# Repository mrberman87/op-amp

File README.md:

# Discrete Operational Amplifier — Two-Stage, LCSC-sourced (Rev E)

A **discrete-component operational amplifier** built only from parts LCSC
stocks. No op-amp ICs: transistors, resistors and capacitors.

Rev E adds a **second gain stage** to Rev D. That is what makes the 60 dB
requirement reachable: the single-stage Rev D topped out at 58.5 dB because
the BFP420's Early voltage (`VAF = 28.4 V`) sets its intrinsic gain at
~60.7 dB. The second stage raises the **open-loop** gain to ~110 dB, so a
60 dB closed loop has ~50 dB of loop gain, and the Miller capacitor sets the
bandwidth.

---

## 1. Target vs. achieved

| Parameter | Target | Rev E | Verdict |
|---|---|---|---|
| Closed-loop gain | 60 dB (1000 V/V) | **59.9 dB** | met |
| −3 dB bandwidth | DC → 10 MHz | **DC → 11.5 MHz** | met |
| Gain at 10 MHz | 60 dB | **58.0 dB** (−2 dB) | ~met |
| Open-loop gain | — | **~110 dB** | — |
| Phase margin | > 45° | **~65°** (no closed-loop peaking) | met |
| Output stage | push-pull | **class-AB complementary** | met |
| Supplies | ±15 V | ±15 V | — |
| ERC | clean | **0 errors / 0 warnings** | met |
| Device stress | no overstress | **no VCEO or >50 % Pd violations** | met |

The closed-loop response is flat (no peaking) from DC to ~1 MHz, −2 dB at
10 MHz, −3 dB at 11.5 MHz. The low-frequency gain is 59.4 dB at 0.01 Hz,
so the AC bypass in stage 2 does **not** introduce an audio-band rolloff in
closed loop.

---

## 2. Topology

```
 IN+ ─┐
      ├─ Q1/Q2 BFP420 diff pair ── Q4/Q6 MMBTH81 mirror ── c2
 IN− ─┘   (Q3 ref-side cascode)    (Q5/Q7 cascodes, Q8 helper)
                                                             │
                        ┌────────────────────────────────────┘
                        ▼
                  Q11 buffer (BFP420 + Q12 cascode) ── d1
                                                             │
                        ┌────────────────────────────────────┘
                        ▼
                  Q13 stage-2 CE (BFP420), R19 load, R20/C6 emitter
                                                             │
                        C7 = 68 p Miller compensation ───────┤
                                                             │
                        ┌────────────────────────────────────┘
                        ▼
                  Q14 buffer (BFP420 + Q15 cascode) ── d3
                                                             │
                        ┌────────────────────────────────────┘
                        ▼
                  Q16/Q18 class-AB push-pull (BFP420 / MMBTH81)
                  Q19 Vbe multiplier, R17 = 47 Ω isolation ── OUT
```

**Why stage 2 is a CE with a bypassed emitter.** A common-emitter stage
needs its emitter at AC ground to have gain. The DC bias needs a defined
current, so the emitter resistor `R20 = 50 Ω` is bypassed by `C6 = 220 µF`.
The bypass corner is ~15 Hz in **open loop**, but the closed-loop 60 dB
response stays flat because the open-loop gain at low frequency (~85 dB) is
still far above 60 dB. The measured closed-loop gain is 59.4 dB at 0.01 Hz.

**Miller compensation.** `C7 = 68 pF` from d1 to d2 sets the dominant pole.
Sweeping it gives the trade-off:

| C7 | closed-loop gain | peaking | f−3dB |
|---|---|---|---|
| 22 pF | 59.9 dB | 3.7 dB | 27.6 MHz |
| 47 pF | 59.9 dB | 0.6 dB | 16.2 MHz |
| **68 pF** | **59.9 dB** | **0 dB** | **11.5 MHz** |
| 100 pF | 59.9 dB | 0 dB | 7.4 MHz |

---

## 3. Devices and LCSC part numbers

| Part | Type | fT | VCEO | Package | LCSC |
|---|---|---|---|---|---|
| BFP420H6327 | NPN | 25 GHz | 4.5 V | SOT-343 | **C412737** |
| MMBTH81 | PNP | 600 MHz | 20 V | SOT-23 | **C190349** |
| MMBT3904 | NPN | 300 MHz | 40 V | SOT-23 | **C20526** |

`BFP420` is a **4.5 V** part, so every BFP420 is cascoded on ±15 V:

- Q1 (input pair, reference side) → Q3
- Q11 (buffer 1) → Q12
- Q13 (stage 2) runs at Vce ≈ 1.9 V, safe
- Q14 (buffer 2) → Q15
- Q16 (output NPN) → Q17

The MMBTH81 mirror/cascode/helper/output-PNP sees ≤ 15.8 V, inside its 20 V
rating.

The three BFP420 emitter followers (Q11, Q14, Q16) each have a 33 Ω base
stopper (R21, R22, R23) right at the base pad: a 25 GHz follower with an
inductive base lead and a capacitive emitter load is a GHz oscillator waiting
to happen. The stoppers move the closed-loop response by < 0.1 %.

### Reference designators

| Ref | Role | Part |
|---|---|---|
| Q1, Q2 | input differential pair | BFP420 |
| Q3 | reference-side cascode | MMBT3904 |
| Q4, Q6 | PNP mirror | MMBTH81 |
| Q5, Q7 | mirror cascodes | MMBTH81 |
| Q8 | regulated-cascode helper | MMBTH81 |
| Q9 | bias-reference diode | MMBT3904 |
| Q10 | tail current source | MMBT3904 |
| Q11 | buffer 1 | BFP420 |
| Q12 | buffer-1 cascode | MMBT3904 |
| Q13 | **stage-2 CE gain** | BFP420 |
| Q14 | buffer 2 | BFP420 |
| Q15 | buffer-2 cascode | MMBT3904 |
| Q16 | output NPN | BFP420 |
| Q17 | output-NPN cascode | MMBT3904 |
| Q18 | output PNP | MMBTH81 |
| Q19 | Vbe multiplier (class-AB bias) | MMBT3904 |
| R1 | bias reference 13.7k | 0603 |
| R2 | bias emitter 1k | 0603 |
| R3 | tail emitter 180 | 0603 |
| R4 | `vcn` divider top 6.8k | 0603 |
| R5 | mirror-ref degeneration 22 | 0603 |
| R6 | helper load 22k | 0603 |
| R7 | load 10k | 0603 |
| R8 | mirror-out degeneration 20 | 0603 |
| R9 | `vcn` divider bottom 8.2k | 0603 |
| R10 | `vcd` divider top 6.8k | 0603 |
| R11 | `vcd` divider bottom 11k | 0603 |
| R12 | Vbe multiplier top 1.8k | 0603 |
| R13 | Vbe multiplier bottom 1.2k | 0603 |
| R14 | PNP base pull-down 10k | 0603 |
| R15 | output NPN emitter 4.7 | 0603 |
| R16 | output PNP emitter 4.7 | 0603 |
| R17 | output isolation 47 | 0603 |
| R18 | tail collector 470 | 0603 |
| **R19** | **stage-2 collector load 1k** | **1206** |
| R20 | stage-2 emitter 50 | 0603 |
| C1, C2 | rail decoupling at J1 100n | 0603 |
| C11, C12 | rail bulk at J1 10 µF, ≥25 V X5R | 1206 |
| C8, C9 | output-collector decoupling (Q17 / Q18) 100n | 0603 |
| C10 | vcd bypass at Q12's base 100n | 0603 |
| C3 | Vbe bypass 100n | 0603 |
| C4, C5 | cascode-bias bypass 100n | 0603 |
| C6 | stage-2 emitter bypass 220 µF | 6.3×5.4 mm |
| C7 | Miller compensation 68 pF | 0603 |
| C13 | stage-2 emitter HF bypass (at Q13) 100n | 0603 |
| C14 | vcd bypass at Q15's base 100n | 0603 |
| R21, R22, R23 | base stoppers (Q11, Q14, Q16) 33 | 0603 |
| **R24** | **feedback 10k, OUTA → INN** | 0603 |
| **R25** | **gain-setting 10, INN → GND** | 0603 |
| TP1–TP8 | test pads: +15V, −15V, GND, vcn, vcd, OUTA, OUT, GND (beside OUT) | Ø1.5 mm SMD |
| J1 | 6-way screw terminal, 3.5 mm (Phoenix PT 1,5/6-3,5-H 1984662 or equivalent): 1 +15V, 2 INP, 3 GND, 4 OUT, 5 INN, 6 −15V | THT |

**The 60 dB gain is set on the board** by R24/R25 (1 + 10k/10 = 1001), taken
from OUTA — before the 47 Ω R17 — exactly as simulated. R17 therefore stays
outside the loop and isolates whatever capacitance hangs on OUT: the netlist
check shows 0.04 dB of peaking with 100 pF on OUT and 0.23 dB with 1 nF. INN
is still on J1 for trimming or paralleling a different gain.

**J1 pin order follows the board.** +15 V (pin 1) lands in the +15 V plane
(top half), −15 V (pin 6) in the −15 V plane (bottom half), and OUT (pin 4)
lines up with the In2.Cu GND corridor that carries OUT/OUTA back on B.Cu.
GND (pin 3) sits between INP (pin 2) and OUT, and doubles as the load
return beside OUT; INN (pin 5) is next to R24/R25 and is low-impedance
(10 Ω R25 to GND), so its neighbour OUT cannot couple into it.

---

## 4. Results (`sim/rf_two_stage.py`)

Closed-loop non-inverting, `Rf = 10 kΩ`, `Rg = 10 Ω` (gain = 1001; on the board these are R24/R25):

| Quantity | Value |
|---|---|
| Closed-loop gain | **59.91 dB** |
| Peaking | **0 dB** |
| f−3dB | **11.46 MHz** (11.47 before the base stoppers) |
| Gain at 10 MHz | **57.96 dB** |
| Gain at 0.01 Hz | 59.42 dB |
| Open-loop gain | ~110 dB |

### Device stress

`sim/stress_two.py` checks every junction and every resistor's dissipation.
All transistors are inside their VCEO and below 50 % of their Pd rating; all
resistors are below the 75 % chip-resistor derating. The hottest parts:

| Device | Vce | Pd | Rating |
|---|---|---|---|
| Q13 (stage-2 CE) | 1.9 V | 23 mW | 4.5 V, 210 mW |
| Q10 (tail) | 7.2 V | 75 mW | 40 V, 200 mW |
| Q3 (input cascode) | 13.6 V | 67 mW | 40 V, 200 mW |
| Q7 (mirror cascode) | 11.8 V | 63 mW | 20 V, 225 mW |
| Q18 (output PNP) | 15.6 V | 38 mW | 20 V, 225 mW |
| R19 (stage-2 load) | — | **156 mW** | **1206 = 250 mW** |
| R1 (bias reference) | — | 55 mW | 0603 = 100 mW |
| R18 (tail collector) | — | 51 mW | 0603 = 100 mW |

**Known thermal asymmetry in the input pair.** Q2 dissipates ~19 mW
(Vce 3.5 V) against Q1's ~8 mW (Vce 1.6 V, cascoded by Q3). On a SOT-343 that
is a few kelvin of junction difference, i.e. several mV of input offset that the
SPICE models (no self-heating) do not show. The layout keeps Q1/Q2 3.5 mm apart
(centres) with shared emitter copper; the circuit fix is a second cascode on Q2's
collector (TODO 4.7).

> **PCB note:** the BFP420 is a 4-lead SOT-343 (1=B, 2=E, 3=C, 4=E). The
> schematic uses KiCad's 3-pin `Q_NPN_BEC` symbol; on the layout, pad 4
> must be tied to pad 2 (emitter).

---

## 5. Known limitations

- **Input bias current ~21 µA.** At a 60 dB closed loop with `Rf = 10 kΩ` (R24)
  this gives ~0.2 V of output offset; the measured output DC is ~0.56 V
  (the ~0.5 mV input offset amplified by 1000). A trim or a servo would
  remove it. Keep the feedback network impedance low.
- **Closed-loop 60 dB requires a low-impedance feedback network** (`Rf` in
  the low-kΩ range). A 1 MΩ feedback resistor would put 21 V across it.
- The schematic and the **PCB are complete, routed and verified**: 4 layers
  (F.Cu signal+parts / In1.Cu GND / In2.Cu +15 V and −15 V with a GND
  corridor between them and a GND edge frame / B.Cu GND), 50 × 40 mm with
  rounded corners, all 67 parts on the top side plus 2 M3 holes and 3
  fiducials, 350 track segments and 132 vias, KiCad DRC 0 violations /
  0 unconnected under the project's net-class rules. OUT and OUTA run on
  B.Cu along the corridor. Nets come
  from the same table that draws the schematic. See TODO §2.
- **Do not use KiCad's "Update PCB from Schematic".** The board is synced from
  `gen_sch_rf.NET` by `place.py`; the schematic's auto-generated net names
  (e.g. `Net-(Q1-C)`) differ from the board's (`a1`), and an update would
  rename the nets and drop the Analog net-class patterns.

---

## 6. Repository layout

```
opamp/
├── README.md
├── gen_sch_rf.py            generator for the Rev-E schematic (source of truth)
├── gen_sch.py               shared symbol/wire emitter
├── opamp.kicad_sch          generated schematic, Rev E (A3)
├── opamp.kicad_pcb          4-layer board, placed and routed (edited in place)
├── place.py                 sync parts/nets from NET, outline, pours, placement
├── route.py                 router: OUT/OUTA corridor, signals, rail fanouts,
│                            rip-up/reroute + tidy passes, stitching, R19 copper
├── freeroute.py             optional Freerouting round trip (DSN prep / SES import)
├── set_stackup.py           physical 4-layer stack-up -> board file
├── set_rules.py             design rules and net classes -> .kicad_pro
├── verify_board.py          board gate (stack, nets, pad 4, pours, keepouts, DRC)
├── gen_pcb.py               original board generator (superseded; do not re-run)
├── pcb_preview.py           placement PNG
├── render_board.py          routed-board PNG (tracks, vias, pads; ratsnest if unrouted)
├── check.sh                 regenerate + ERC + sims + rules + stack-up + board gate
├── sim/
│   ├── rf_two_stage.py      Rev-E two-stage netlist + closed-loop test
│   ├── stress_two.py        Vce / Pd check for Rev E (every transistor and resistor)
│   ├── verify_netlist.py    closed-loop + capacitive-load test on the schematic netlist
│   ├── rf_lcsc.py           Rev-D single-stage netlist (models live here)
│   └── …                    earlier experiments
├── analysis/  docs/  artifacts/  svg/
```

---

## 7. How to run

```bash
# regenerate the schematic
python3 gen_sch_rf.py

# design-rule check — must report 0 violations
kicad-cli sch erc --severity-all -o /tmp/erc.rpt opamp.kicad_sch

# schematic -> SPICE netlist
kicad-cli sch export netlist --format spice -o /tmp/opamp.cir opamp.kicad_sch

# closed-loop spec test (60 dB, bandwidth, peaking)
cd sim && python3 rf_two_stage.py

# device stress
cd sim && python3 stress_two.py

# everything
./check.sh
```

The exported netlist was verified to reproduce `sim/rf_two_stage.py`
exactly: **59.91 dB, no peaking, 11.46 MHz**.

---

## 8. References

Local copies under `docs/` (scanned; OCR sidecars in `docs/ocr/`):

- *Operational Amplifiers — Design and Applications* (Tobey/Graeme/Huelsman/Burr-Brown)
- *Analog Integrated Circuit Design* (Johns & Martin)
- *Analysis and Design of Analog Integrated Circuits* (Gray & Meyer)
- *Microelectronic Circuits* (Sedra & Smith)
- *The Art of Electronics*, 2nd ed. (Horowitz & Hill)

## 9. Tooling

- KiCad 10.0.6, `kicad-cli`, `pcbnew`
- ngspice 45.2
- Python 3 (`math`/`subprocess` only for the sims)

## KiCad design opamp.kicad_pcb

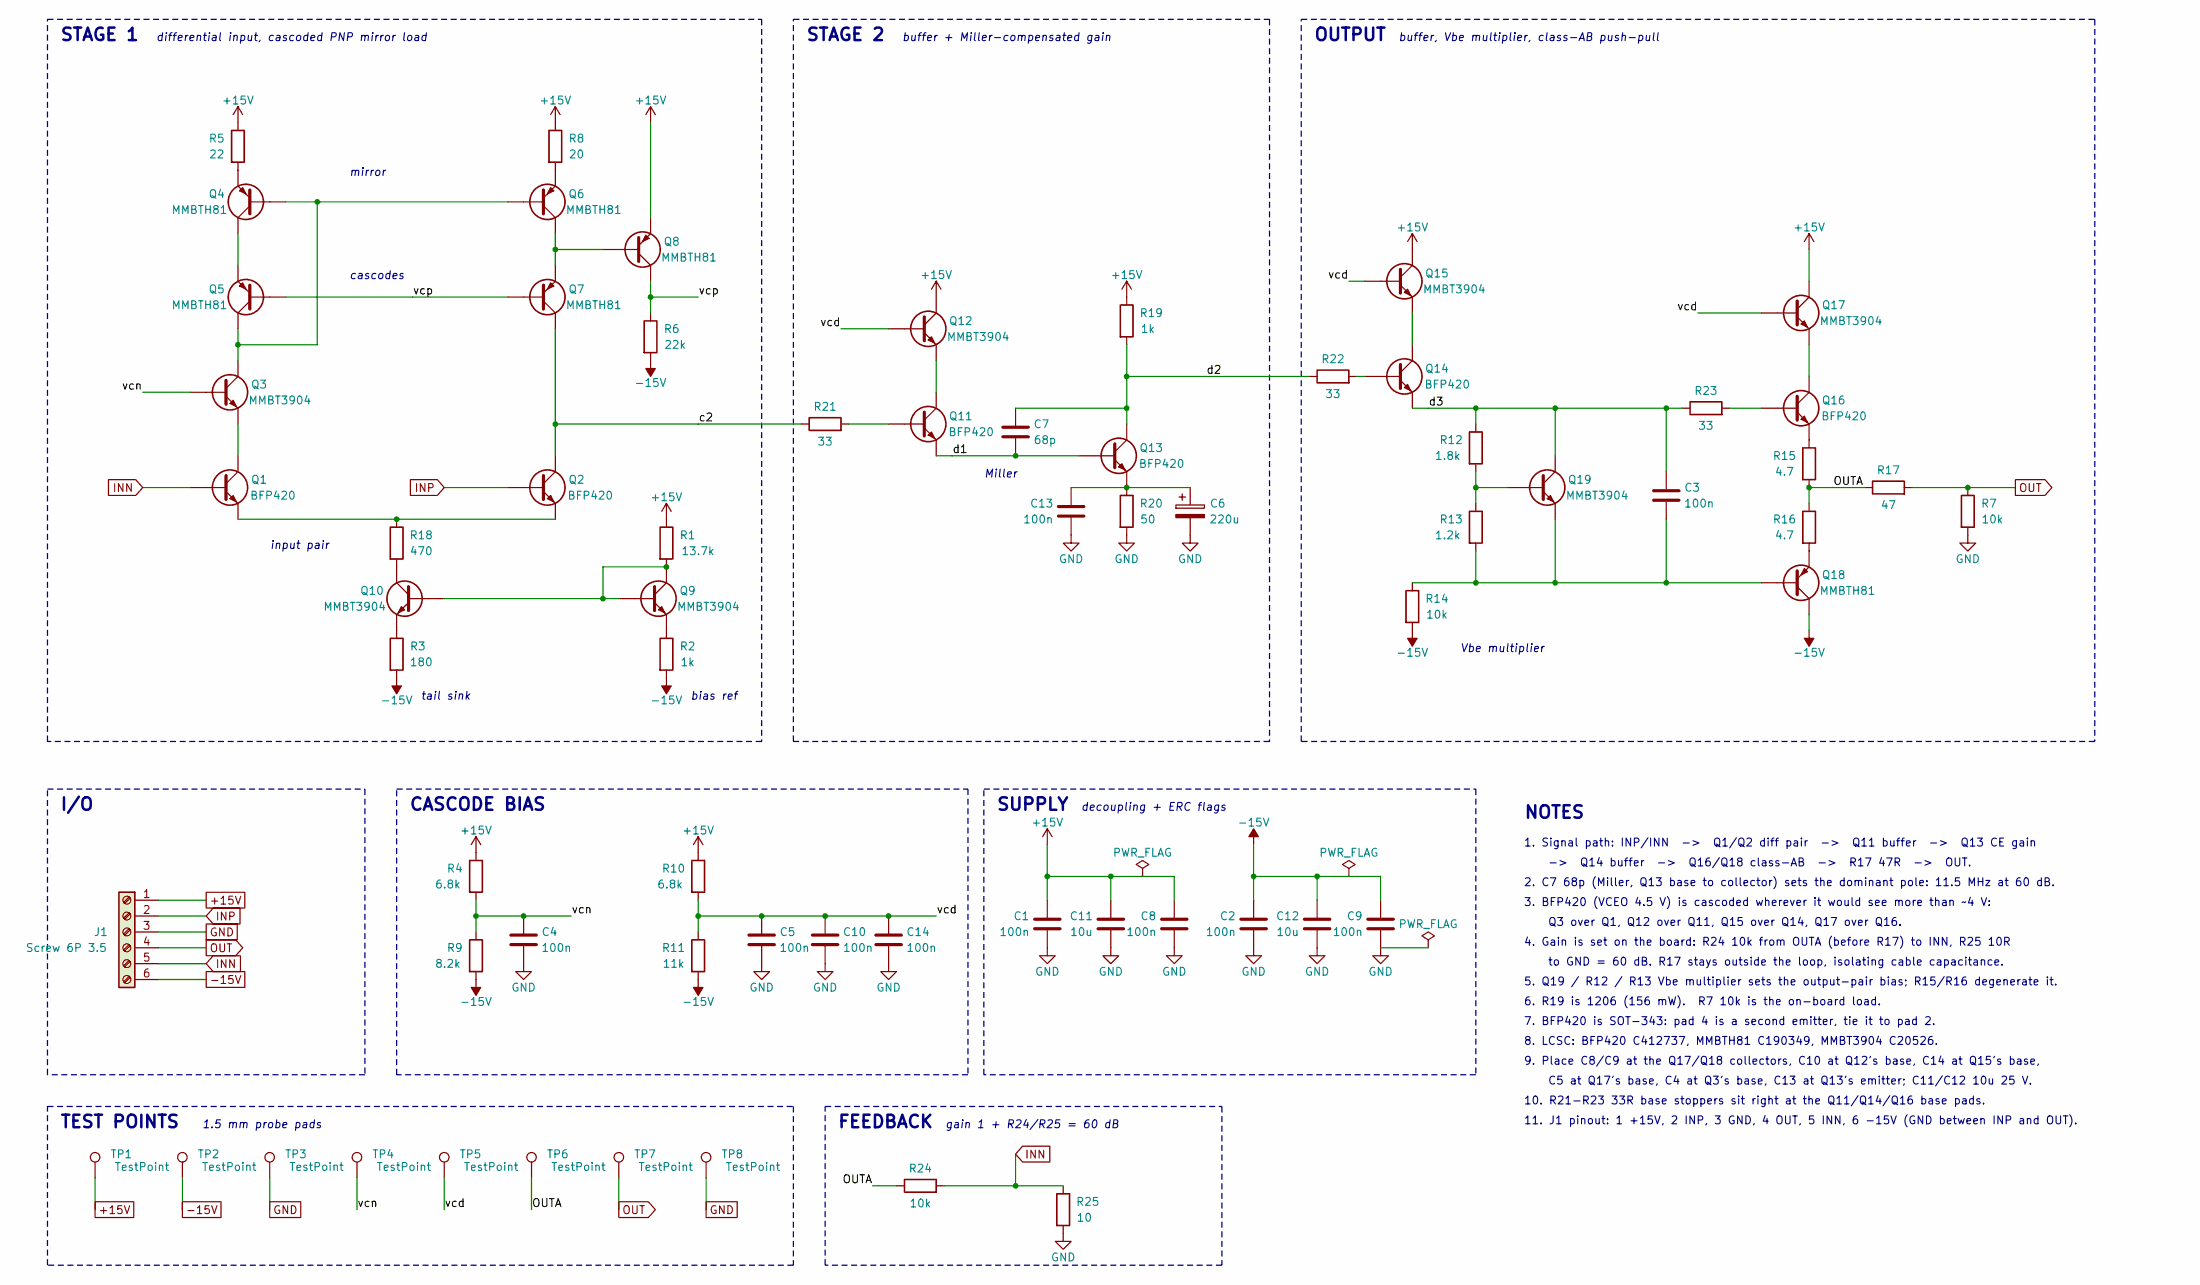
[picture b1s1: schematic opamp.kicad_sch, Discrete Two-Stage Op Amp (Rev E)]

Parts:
C1, C2, C3, C4, C5, C8, C9, C10, C13, C14: 100n; C_0603_1608Metric
C6: 220u; CP_Elec_6.3x5.4
C7: 68p; C_0603_1608Metric
C11, C12: 10u; C_1206_3216Metric
J1: Screw 6P 3.5; TerminalBlock_Phoenix_PT-1,5-6-3.5-H_1x06_P3.50mm_Horizontal
Q1, Q2, Q11, Q13, Q14, Q16: BFP420; SOT-343_SC-70-4; MPN BFP420; LCSC C412737
Q3, Q9, Q10, Q12, Q15, Q17, Q19: MMBT3904; SOT-23; MPN MMBT3904; LCSC C20526
Q4, Q5, Q6, Q7, Q8, Q18: MMBTH81; SOT-23; MPN MMBTH81; LCSC C190349
R1: 13.7k; R_0603_1608Metric
R2: 1k; R_0603_1608Metric
R3: 180; R_0603_1608Metric
R4, R10: 6.8k; R_0603_1608Metric
R5: 22; R_0603_1608Metric
R6: 22k; R_0603_1608Metric
R7, R14, R24: 10k; R_0603_1608Metric
R8: 20; R_0603_1608Metric
R9: 8.2k; R_0603_1608Metric
R11: 11k; R_0603_1608Metric
R12: 1.8k; R_0603_1608Metric
R13: 1.2k; R_0603_1608Metric
R15, R16: 4.7; R_0603_1608Metric
R17: 47; R_0603_1608Metric
R18: 470; R_0603_1608Metric
R19: 1k; R_1206_3216Metric
R20: 50; R_0603_1608Metric
R21, R22, R23: 33; R_0603_1608Metric
R25: 10; R_0603_1608Metric
TP1, TP2, TP3, TP4, TP5, TP6, TP7, TP8: TestPoint; TestPoint_Pad_D1.5mm

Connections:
+15V: C1.1, C8.1, C11.1, J1.1, Q8.2 (E), Q12.3 (C), Q15.3 (C), Q17.3 (C), R1.1, R4.1, R5.1, R8.1, R10.1, R19.1, TP1.1
-15V: C2.1, C9.1, C12.1, J1.6, Q18.3 (C), R2.2, R3.2, R6.2, R9.2, R11.2, R14.2, TP2.1
GND: C1.2, C2.2, C4.2, C5.2, C6.2, C8.2, C9.2, C10.2, C11.2, C12.2, C13.2, C14.2, J1.3, R7.2, R20.2, R25.2, TP3.1, TP8.1
INN: J1.5, Q1.1 (B), R24.2, R25.1
INP: J1.2, Q2.1 (B)
OUT: J1.4, R7.1, R17.2, TP7.1
OUTA: R15.2, R16.1, R17.1, R24.1, TP6.1
T: Q1.2 (E), Q1.4, Q2.2 (E), Q2.4, R18.1
Tc: Q10.3 (C), R18.2
a1: Q1.3 (C), Q3.2 (E)
b9: C3.2, Q18.1 (B), Q19.2 (E), R13.2, R14.1
c1: Q3.3 (C), Q4.1 (B), Q5.3 (C), Q6.1 (B)
c2: Q2.3 (C), Q7.3 (C), R21.1
c2b: Q11.1 (B), R21.2
d1: C7.2, Q11.2 (E), Q11.4, Q13.1 (B)
d2: C7.1, Q13.3 (C), R19.2, R22.1
d2b: Q14.1 (B), R22.2
d3: C3.1, Q14.2 (E), Q14.4, Q19.3 (C), R12.1, R23.1
d3b: Q16.1 (B), R23.2
db: Q19.1 (B), R12.2, R13.1
e1: C6.1, C13.1, Q13.2 (E), Q13.4, R20.1
e3: Q4.2 (E), R5.2
e4: Q6.2 (E), R8.2
n1: Q4.3 (C), Q5.2 (E)
n2: Q6.3 (C), Q7.2 (E), Q8.1 (B)
n8: Q16.2 (E), Q16.4, R15.1
n9: Q18.2 (E), R16.2
vcd: C5.1, C10.1, C14.1, Q12.1 (B), Q15.1 (B), Q17.1 (B), R10.2, R11.1, TP5.1
vcn: C4.1, Q3.1 (B), R4.2, R9.1, TP4.1
vcp: Q5.1 (B), Q7.1 (B), Q8.3 (C), R6.1
veb: Q9.2 (E), R2.1
vet: Q10.2 (E), R3.1
vref: Q9.1 (B), Q9.3 (C), Q10.1 (B), R1.2
x8: Q11.3 (C), Q12.2 (E)
x9: Q14.3 (C), Q15.2 (E)
xo: Q16.3 (C), Q17.2 (E)

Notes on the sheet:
STAGE 1
differential input, cascoded PNP mirror load
STAGE 2
buffer + Miller-compensated gain
OUTPUT
buffer, Vbe multiplier, class-AB push-pull
I/O
CASCODE BIAS
SUPPLY
decoupling + ERC flags
TEST POINTS
1.5 mm probe pads
FEEDBACK
gain 1 + R24/R25 = 60 dB
NOTES
1. Signal path: INP/INN -> Q1/Q2 diff pair -> Q11 buffer -> Q13 CE gain
-> Q14 buffer -> Q16/Q18 class-AB -> R17 47R -> OUT.
2. C7 68p (Miller, Q13 base to collector) sets the dominant pole: 11.5 MHz at 60 dB.
3. BFP420 (VCEO 4.5 V) is cascoded wherever it would see more than ~4 V:
Q3 over Q1, Q12 over Q11, Q15 over Q14, Q17 over Q16.
4. Gain is set on the board: R24 10k from OUTA (before R17) to INN, R25 10R
to GND = 60 dB. R17 stays outside the loop, isolating cable capacitance.
5. Q19 / R12 / R13 Vbe multiplier sets the output-pair bias; R15/R16 degenerate it.
6. R19 is 1206 (156 mW). R7 10k is the on-board load.
7. BFP420 is SOT-343: pad 4 is a second emitter, tie it to pad 2.
8. LCSC: BFP420 C412737, MMBTH81 C190349, MMBT3904 C20526.
9. Place C8/C9 at the Q17/Q18 collectors, C10 at Q12's base, C14 at Q15's base,
C5 at Q17's base, C4 at Q3's base, C13 at Q13's emitter; C11/C12 10u 25 V.
10. R21-R23 33R base stoppers sit right at the Q11/Q14/Q16 base pads.
11. J1 pinout: 1 +15V, 2 INP, 3 GND, 4 OUT, 5 INN, 6 -15V (GND between INP and OUT).
mirror
cascodes
input pair
tail sink
bias ref
Miller
Vbe multiplier

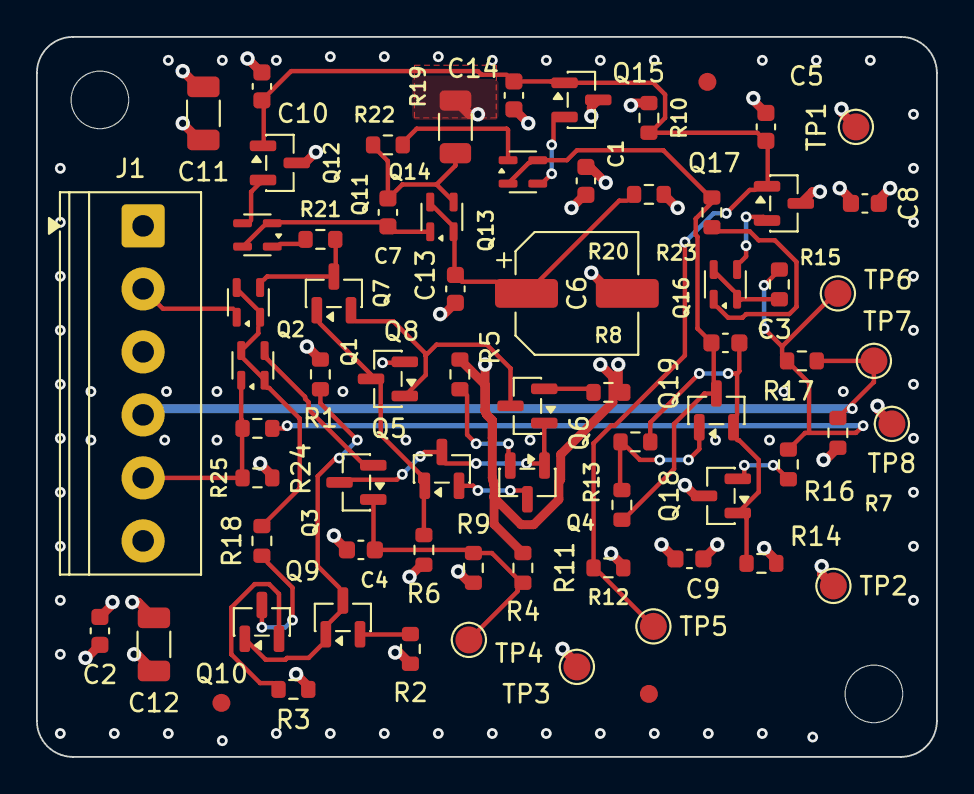
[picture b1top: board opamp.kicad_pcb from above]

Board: 4 copper layers, 50.0 x 40.0 mm, 72 parts (0 on the bottom side), 36 nets.

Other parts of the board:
FID1, FID2, FID3: Fiducial; Fiducial_1mm_Mask2mm
H1, H2: MountingHole; MountingHole_3.2mm_M3

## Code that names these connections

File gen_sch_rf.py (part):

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  * Support circuits sit in a lower band: the I/O connector, the two cascode
    bias dividers and the supply decoupling.
  * Only nets that genuinely jump across the sheet carry a label: the
    connector pins (INP, INN, OUT, rails) and the bias lines vcn, vcd, vcp.
  * Every reference and value is placed next to its part, never left to an
    auto-placer.

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_GRID = {c[0]: (c[3], c[4]) for c in _PLACE}

NET = {
    # GND (pin 2) and INN (pin 3) sit between the non-inverting input and the
    # output, so the terminal cannot couple OUT back into INP (positive
    # feedback at 60 dB); OUT next to INN is negative feedback, harmless
    ("J1", "1"): "+15V", ("J1", "2"): "INP", ("J1", "3"): "GND",
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    wire(("Q5", "3"), ("Q3", "3"))
    # cascode base line vcp; Q8/R6 generate it on the right
    wire(("Q5", "1"), (64, 48), ("Q7", "1"))
    label("vcp", 64, 48)
    wire(("Q8", "3"), ("R6", "1"))
    wire((94, 48), (100, 48))
    label("vcp", 100, 48)
    # input pair with Q3 cascoding Q1
    wire(("Q3", "2"), ("Q1", "3"))                     # a1
    wire(("Q7", "3"), ("Q2", "3"))                     # c2 column
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    wire(("Q2", "1"), (68, 72))
    port("INP", 68, 72, "right")
    wire(("Q3", "1"), (30, 60))
    label("vcn", 30, 60, "right")
    # tail: R18 off the middle of the emitter bus, Q10 sink, Q9 reference
    wire(("Q10", "1"), ("Q9", "1"))                    # vref base line
    wire(("Q9", "3"), (88, 82), (88, 86))              # Q9 diode strap
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    wire(("Q13", "2"), ("C6", "1"))                    # e1 -> bypass cap
    wire(("C13", "1"), ("Q13", "2"))                   # ceramic in parallel
    wire(("Q12", "1"), (118, 52))
    label("vcd", 118, 52, "right")

    # ===================== stage 2 -> output: d2 ======================
    wire((154, 58), ("R22", "1"))
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    wire(("Q15", "2"), ("Q14", "3"))                   # x9
    wire(("Q17", "2"), ("Q16", "3"))                   # xo
    wire(("Q15", "1"), (182, 46))
    label("vcd", 182, 46, "right")
    wire(("Q17", "1"), (226, 50))
    label("vcd", 226, 50, "right")
    # d3: one horizontal from Q14's emitter to Q16's base, with three drops
    wire(("Q14", "2"), ("R23", "1"))
    wire(("R23", "2"), ("Q16", "1"))
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    # emitter resistors meet at OUTA, then R17 and the load to OUT
    wire(("R15", "2"), ("R16", "1"))
    wire((240, 72), ("R17", "1"))
    label("OUTA", 243, 72)
    wire(("R17", "2"), ("R7", "1"), (266, 72))
    port("OUT", 266, 72)

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    # ======================= lower band: feedback ======================
    # OUTA -> R24 -> INN node -> R25 -> GND, drawn left to right
    wire((122, 160), ("R24", "1"))
    label("OUTA", 122, 160, "right")
    wire(("R24", "2"), (146, 160))
    wire((146, 160), ("R25", "1"))
    wire((140, 160), (140, 156))
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    "9. Place C8/C9 at the Q17/Q18 collectors, C10 at Q12's base, C14 at Q15's base,",
    "    C5 at Q17's base, C4 at Q3's base, C13 at Q13's emitter; C11/C12 10u 25 V.",
    "10. R21-R23 33R base stoppers sit right at the Q11/Q14/Q16 base pads.",
    "11. J1 pinout: 1 +15V, 2 INP, 3 GND, 4 OUT, 5 INN, 6 -15V (GND between INP and OUT).",
]

# small italic annotations naming sub-circuits: (text, grid x, grid y)
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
